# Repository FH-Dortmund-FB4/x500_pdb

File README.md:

# LM21305-Based Power Distribution Board

## Overview

This project describes a compact power distribution board (PDB) for multicopter applications. The design is based on the LM21305 synchronous buck regulator and provides regulated 5 V outputs alongside direct battery connections.

The board follows a 30 × 30 mm mounting pattern, compatible with standard flight controller stacks.

## Features

- LM21305-based DC-DC regulation
- 30 × 30 mm mounting pattern
- Maximum output current: 5 A
- 3 × regulated 5 V outputs (JST-PH 2.0)
- 2 × battery outputs (JST-PH 2.0)

## Specifications

| Parameter         | Value                  |
|------------------|------------------------|
| Input Voltage     | 3 V – 18 V             |
| Regulated Output  | 5 V                    |
| Maximum Current   | 5 A (total)            |
| Mounting Pattern  | 30 × 30 mm             |
| Connectors        | JST-PH 2.0             |

## LM21305 Regulator Summary

The LM21305 is a synchronous step-down (buck) DC-DC converter with integrated power MOSFETs and peak current-mode control. :contentReference[oaicite:0]{index=0}  

Key characteristics:

- Input voltage range: 3 V to 18 V 
- Output current capability: up to 5 A 
- Adjustable switching frequency: 300 kHz to 1.5 MHz
- Integrated high-side and low-side MOSFETs 

Functional features:

- Peak current-mode control for fast transient response 
- Internal soft-start and enable control
- Cycle-by-cycle overcurrent protection and thermal shutdown
- Overvoltage and undervoltage protection

These characteristics enable high efficiency and compact external component selection.

## Electrical Interfaces

### 5 V Outputs (3×)
- 5 V
- Ground

### Battery Outputs (2×)
- VBAT
- Ground

## Mechanical Details

- Mounting hole spacing:  30 mm × 30 mm (M3 compatible)

## Contributions

Contributions and issue reports are welcome.

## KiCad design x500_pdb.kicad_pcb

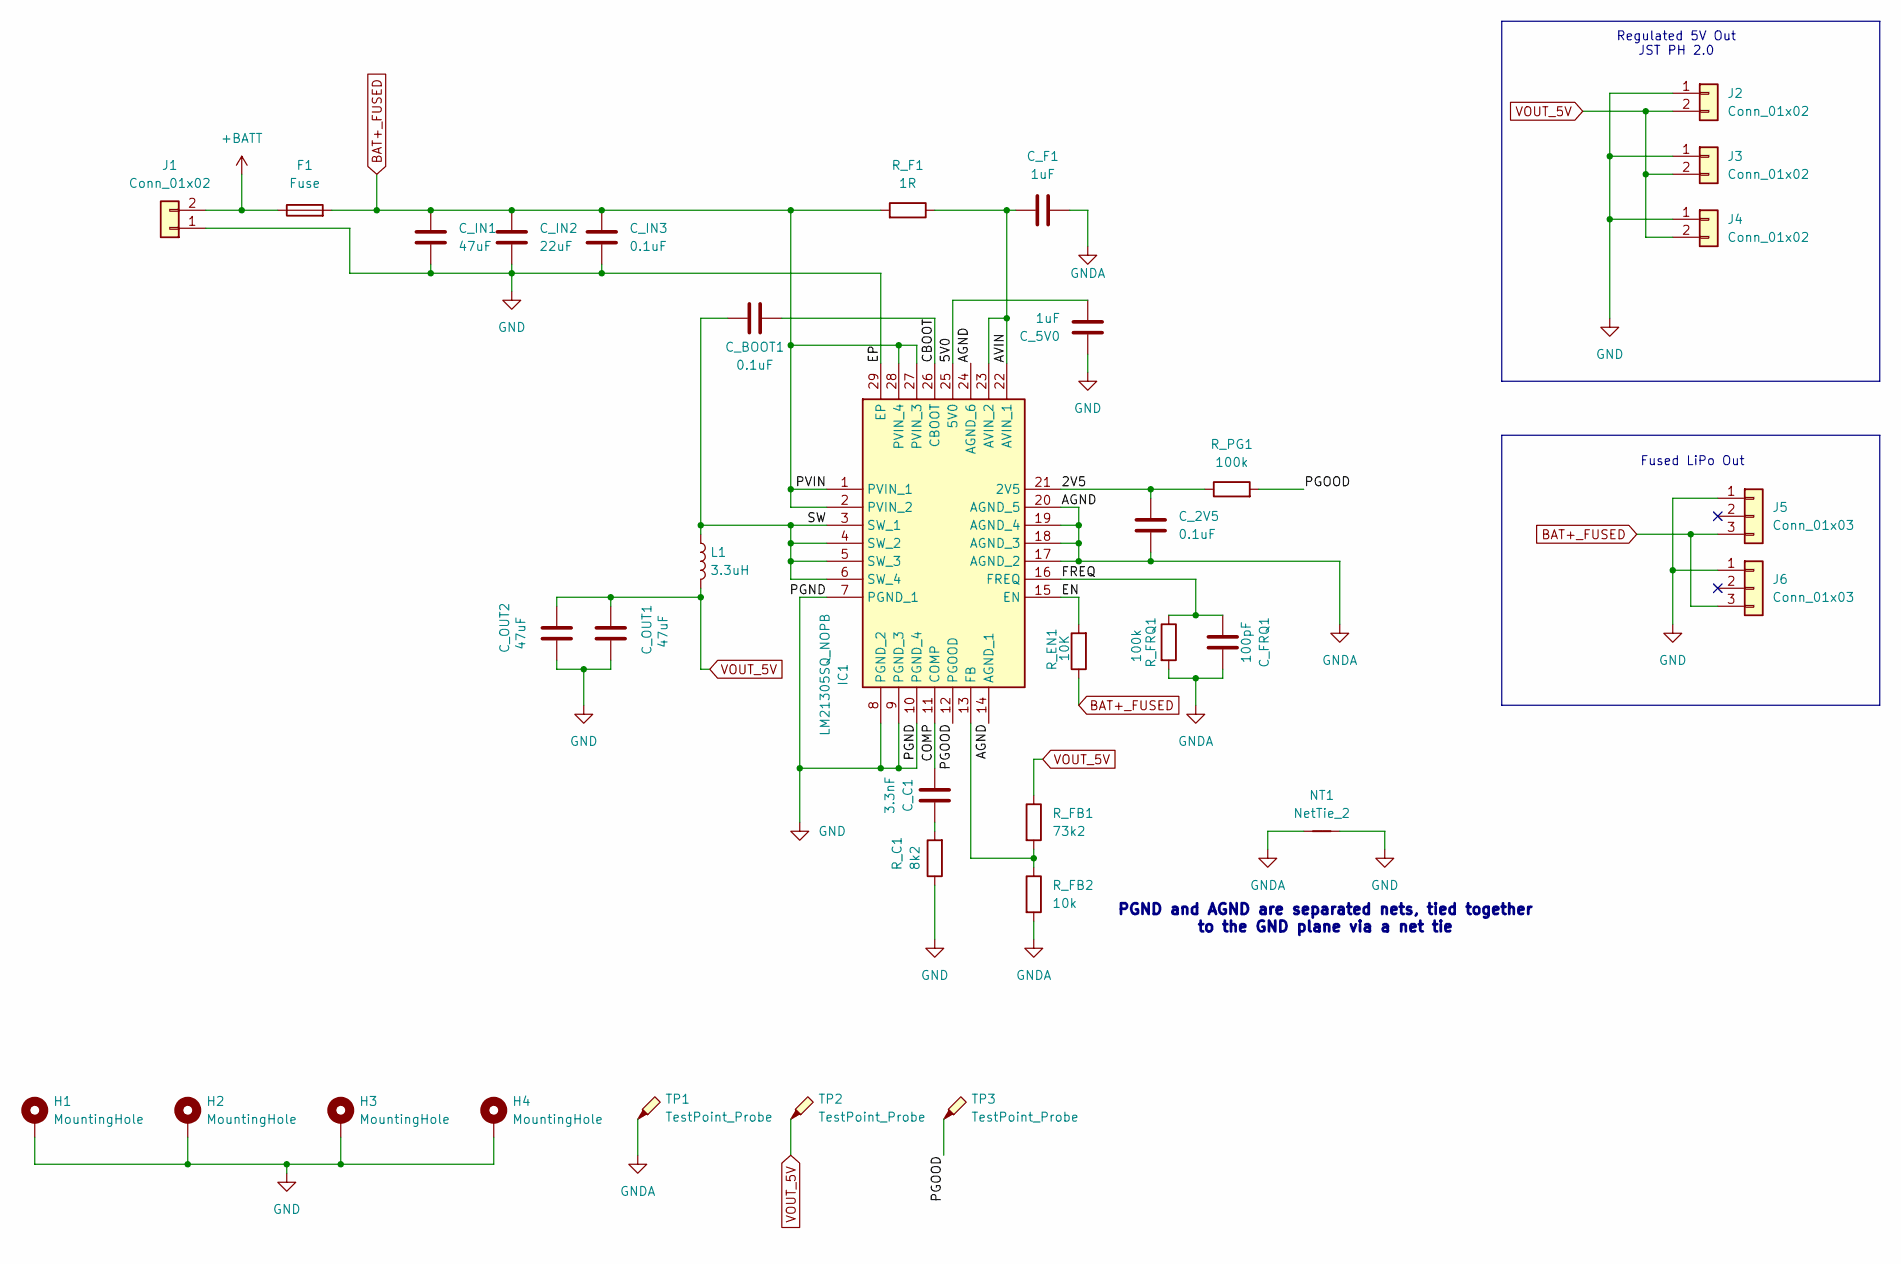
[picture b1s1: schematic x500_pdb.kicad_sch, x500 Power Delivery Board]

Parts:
C_2V5: 0.1uF; C_0603_1608Metric_Pad1.08x0.95mm_HandSolder; Mouser Part Number 80-C0603X104J4RECAUT
C_5V0: 1uF; C_0603_1608Metric_Pad1.08x0.95mm_HandSolder; Mouser Part Number 80-C0603X105J4R
C_BOOT1: 0.1uF; C_0603_1608Metric_Pad1.08x0.95mm_HandSolder; Mouser Part Number 80-C0603X104J4RECAUT
C_C1: 3.3nF; C_0603_1608Metric_Pad1.08x0.95mm_HandSolder; Mouser Part Number 581-0603YC332JAT2A
C_F1: 1uF; C_0603_1608Metric_Pad1.08x0.95mm_HandSolder; Mouser Part Number 187-CL10B105KA8NNWC
C_FRQ1: 100pF; C_0603_1608Metric_Pad1.08x0.95mm_HandSolder; Mouser Part Number 581-06033C101JAT4A
C_IN1: 47uF; CP_EIA-7343-20_Kemet-V_HandSolder; Mouser Part Number 80-T495D476K25ATE120
C_IN2: 22uF; C_1210_3225Metric_Pad1.33x2.70mm_HandSolder; Mouser Part Number 81-GRM32ER61E226KE15
C_IN3: 0.1uF; C_1206_3216Metric_Pad1.33x1.80mm_HandSolder; Mouser Part Number 81-GCJ31MR71E104KA1L
C_OUT1, C_OUT2: 47uF; C_1206_3216Metric_Pad1.33x1.80mm_HandSolder; Mouser Part Number 81-GRM31CR61A476KE5L
F1: Fuse; Fuse_1206_3216Metric; Mouser Part Number 652-SF-1206F250M-2
H1, H2, H3, H4: MountingHole; MountingHole_3.2mm_M3_DIN965_Pad_TopBottom
IC1: LM21305SQ_NOPB; QFN50P500X500X80-29N; Mouser Part Number 926-LM21305SQ/NOPB
J1: Conn_01x02; CONN-TH_XT60PW-M
J2, J3, J4: Conn_01x02; JST_PH_S2B-PH-K_1x02_P2.00mm_Horizontal; Mouser Part Number 306-S2BPHKSLFSNPP
J5, J6: Conn_01x03; JST_PH_S3B-PH-K_1x03_P2.00mm_Horizontal; Mouser Part Number 306-S3BPHKSLFSN
L1: 3.3uH; L_7.3x7.3_H3.5; Mouser Part Number 652-SRP7050WA-3R3M
NT1: NetTie_2; NetTie-2_SMD_Pad2.0mm
R_C1: 8k2; R_0603_1608Metric_Pad0.98x0.95mm_HandSolder; Mouser Part Number 652-CR0603FX-8201ELF
R_EN1: 10K; R_1206_3216Metric_Pad1.30x1.75mm_HandSolder; Mouser Part Number 756-WCR1206-10KFA
R_F1: 1R; C_0603_1608Metric_Pad1.08x0.95mm_HandSolder; Mouser Part Number 667-ERJ-3GEYJ1R0V
R_FB1: 73k2; R_0603_1608Metric_Pad0.98x0.95mm_HandSolder; Mouser Part Number 660-RN73H1JT7232F100
R_FB2: 10k; R_0603_1608Metric_Pad0.98x0.95mm_HandSolder; Mouser Part Number 71-CRCW060310K0FKEI
R_FRQ1: 100k; R_0603_1608Metric_Pad0.98x0.95mm_HandSolder; Mouser Part Number 594-MCT06030C1003FP5
R_PG1: 100k; R_0603_1608Metric_Pad0.98x0.95mm_HandSolder; Mouser Part Number 594-MCT06030C1003FP5
TP1, TP2, TP3: TestPoint_Probe; TestPoint_Pad_1.5x1.5mm

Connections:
+BATT: F1.1, J1.2
/2V5: C_2V5.1, IC1.21 (2V5), R_PG1.1
/5V0: C_5V0.2, IC1.25 (5V0)
/AVIN: C_F1.1, IC1.22 (AVIN_1), IC1.23 (AVIN_2), R_F1.1
/CBOOT: C_BOOT1.2, IC1.26 (CBOOT)
/COMP: C_C1.2, IC1.11 (COMP)
/EN: IC1.15 (EN), R_EN1.2
/FREQ: C_FRQ1.1, IC1.16 (FREQ), R_FRQ1.1
/PGOOD: IC1.12 (PGOOD), R_PG1.2, TP3.1
/SW: C_BOOT1.1, IC1.3 (SW_1), IC1.4 (SW_2), IC1.5 (SW_3), IC1.6 (SW_4), L1.1
BAT+_FUSED: C_IN1.1, C_IN2.1, C_IN3.1, F1.2, IC1.1 (PVIN_1), IC1.2 (PVIN_2), IC1.27 (PVIN_3), IC1.28 (PVIN_4), J5.3, J6.3, R_EN1.1, R_F1.2
GND: C_5V0.1, C_IN1.2, C_IN2.2, C_IN3.2, C_OUT1.1, C_OUT2.1, H1.1, H2.1, H3.1, H4.1, IC1.7 (PGND_1), IC1.8 (PGND_2), IC1.9 (PGND_3), IC1.10 (PGND_4), IC1.29 (EP), J1.1, J2.1, J3.1, J4.1, J5.1, J6.1, NT1.2, R_C1.1
GNDA: C_2V5.2, C_F1.2, C_FRQ1.2, IC1.14 (AGND_1), IC1.17 (AGND_2), IC1.18 (AGND_3), IC1.19 (AGND_4), IC1.20 (AGND_5), IC1.24 (AGND_6), NT1.1, R_FB2.2, R_FRQ1.2, TP1.1
unnamed: C_C1.1, R_C1.2
unnamed: IC1.13 (FB), R_FB1.2, R_FB2.1
VOUT_5V: C_OUT1.2, C_OUT2.2, J2.2, J3.2, J4.2, L1.2, R_FB1.1, TP2.1

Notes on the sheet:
Regulated 5V Out JST PH 2.0
Fused LiPo Out
PGND and AGND are separated nets, tied together to the GND plane via a net tie

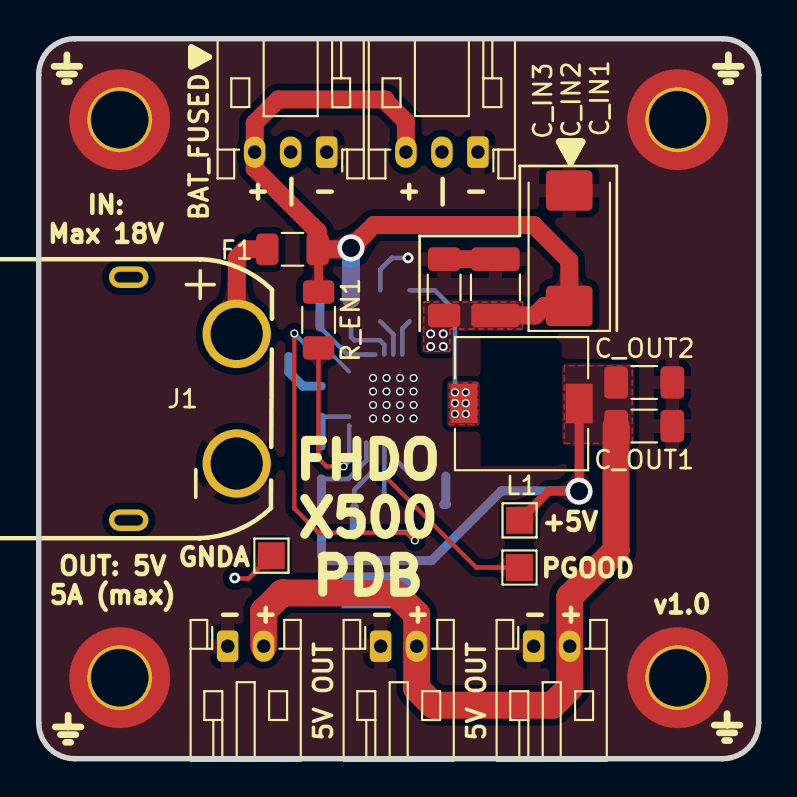
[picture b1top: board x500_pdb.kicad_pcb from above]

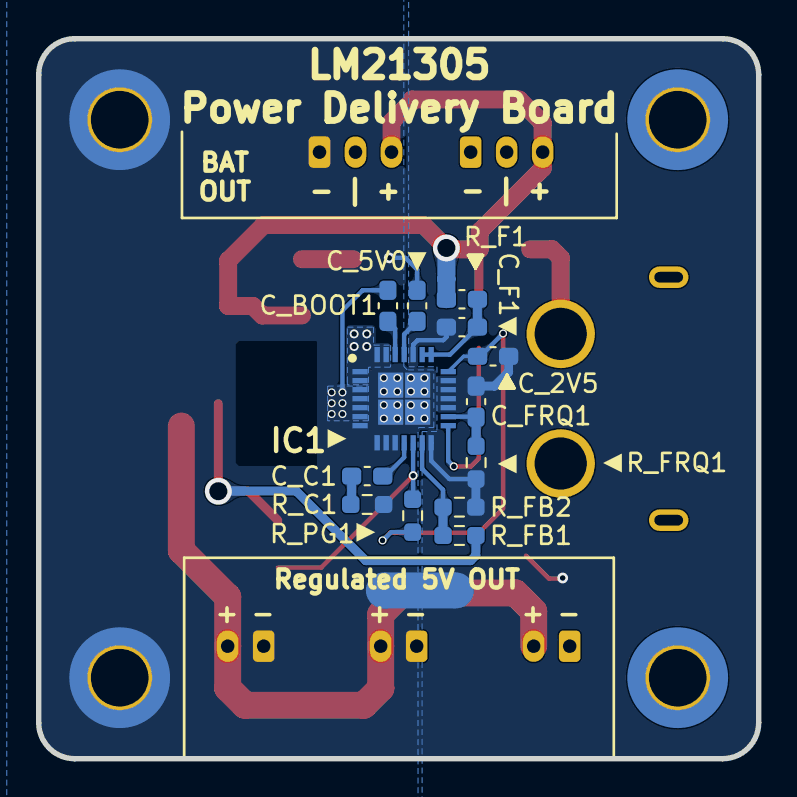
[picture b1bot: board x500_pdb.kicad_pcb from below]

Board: 4 copper layers, 40.0 x 40.0 mm, 35 parts (14 on the bottom side), 16 nets.

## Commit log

2025-11-07 gitignore added
2025-11-07 4 Layers
2025-11-07 Changed gitignore, fp-lib and sym-lib are necessary
2025-11-07 Added Doc
2025-11-07 Lib tables to save project specific lib locations
2025-11-07 Added JLCPCB design rules (also apply to Aisler)
2025-11-07 Started routing
2025-11-07 Prettying up schematics
2025-11-18 Changing certain lines from +BATT to +BAT_FUSED
2025-11-18 Updating PCB
2025-11-18 Add NetTie Footprint
2025-11-18 Cleaning up GND split layer
2025-11-18 Clearing up violations
2025-11-18 Change mounting holes to plated ones
2025-11-18 1.0-RC1. Need to move input caps closer
2025-11-20 Adding picture
2025-11-20 1.0-RC2 Moving input caps close to IC, rearranging components
2025-11-20 1.0-RC2 Fixed Back Silkscreen
2025-11-26 Adding Imports
2025-11-26 Adding BAT_FUSED Outputs
2025-11-26 1.0-RC3 Passing DRC
2025-12-02 1.0-RC3 Assigning Mouser Pt.No.
2025-12-03 Added Mouser Part-Numbers except XT60-Connector
2026-01-27 Adding scope shots
2026-02-13 Remove unused via and trace
2026-03-23 Add files via upload
    Add picture
2026-05-22 KiCad10.0 compatible Save
